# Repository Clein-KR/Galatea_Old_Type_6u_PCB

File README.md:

# Galatea Old Type 6u PCB

<br />

Geonworks에서 판매했던 Studio Kestra의 Galatea 구형 버전과 호환되는 a87 TKL 유니버셜 PCB입니다.

<br />

**Rendering**

<br />

**Prototype**

<br />

**Detail**

<br />

**Compatibility Test**

<br />
<br />

## Supported Layout

<br />

해당 PCB는 ISO 배열을 지원하지 않으며, 6.25u 대신 6u 하단열을 지원합니다.

<br />

<br />

또한 기존의 LED 인디케이터를 모두 버리고 Insert 키 위치에 캡스락 LED 인디케이터를 1개 배치하였습니다. 아래는 Vial의 탭댄스 기능을 활용한 인디케이터 테스트 영상입니다.

<br />

[LED_Indicator_with_Tap_Dance.webm](https://github.com/user-attachments/assets/71b8654c-97a3-42a6-80ce-c4df9c4b528a)

<br />
<br />

## Firmware

<br />

펌웨어는 QMK를 기반으로 Via와 Vial을 지원합니다. 펌웨어 소스코드와 Hex 파일은 [여기](/Firmware)에서 다운로드 받으실 수 있습니다.

<br />

```bash
├── Firmware/
│   ├── clein_galatea_old_type_rev_1_0_via.hex
│   └── clein_galatea_old_type_rev_1_0_vial.hex
└── README.md
```

<br />
<br />

## PCB Guide

<br />

PCB와 호환 보강판 제작에 관련된 가이드 도면은 [여기](/Guide)에서 다운로드 받으실 수 있습니다.

<br />

```bash
├── Guide/
│   ├── PCB_Guideline.dxf
│   ├── PCB_Outline.dxf
│   └── Plate_Guideline.dxf
└── README.md
```

<br />
<br />

## How to Order

<br />

해당 PCB의 프로토타입은 [PCBWay](https://pcbway.com)를 통해 제작되었습니다. 프로토타입 제작에 사용되는 파일들은 [여기](/Production)에서 다운로드 받으실 수 있습니다.

<br />

```bash
├── Production/
│   ├── Galatea_Old_Type_6u_PCB_BOM.csv
│   ├── Galatea_Old_Type_6u_PCB_BOM.xlsx
│   ├── Galatea_Old_Type_6u_PCB_Pos_JLCPCB.csv
│   ├── Galatea_Old_Type_6u_PCB_Pos.csv
│   └── Gerber.zip
└── README.md
```

<br />

아래는 적용된 옵션입니다.

<br />
<br />

## Licence

<br />

해당 프로젝트는 [ai03](https://github.com/ai03-2725) 님의 [KBD8X-MKII-PCB](https://github.com/ai03-2725/KBD8X-MKII-PCB) 프로젝트와 [Joe Scotto](https://github.com/joe-scotto) 님의 [ScottoKeebs](https://github.com/joe-scotto/scottokeebs) 프로젝트를 기반으로 만들어졌습니다. 해당 프로젝트를 활용한 수정, 복제, 배포 등의 활동은 저작자 표시와 함께 비영리적인 목적에 한해서만 가능하며, 라이선스 전문은 [여기](/LICENCE)에서 보실 수 있습니다.

<br />

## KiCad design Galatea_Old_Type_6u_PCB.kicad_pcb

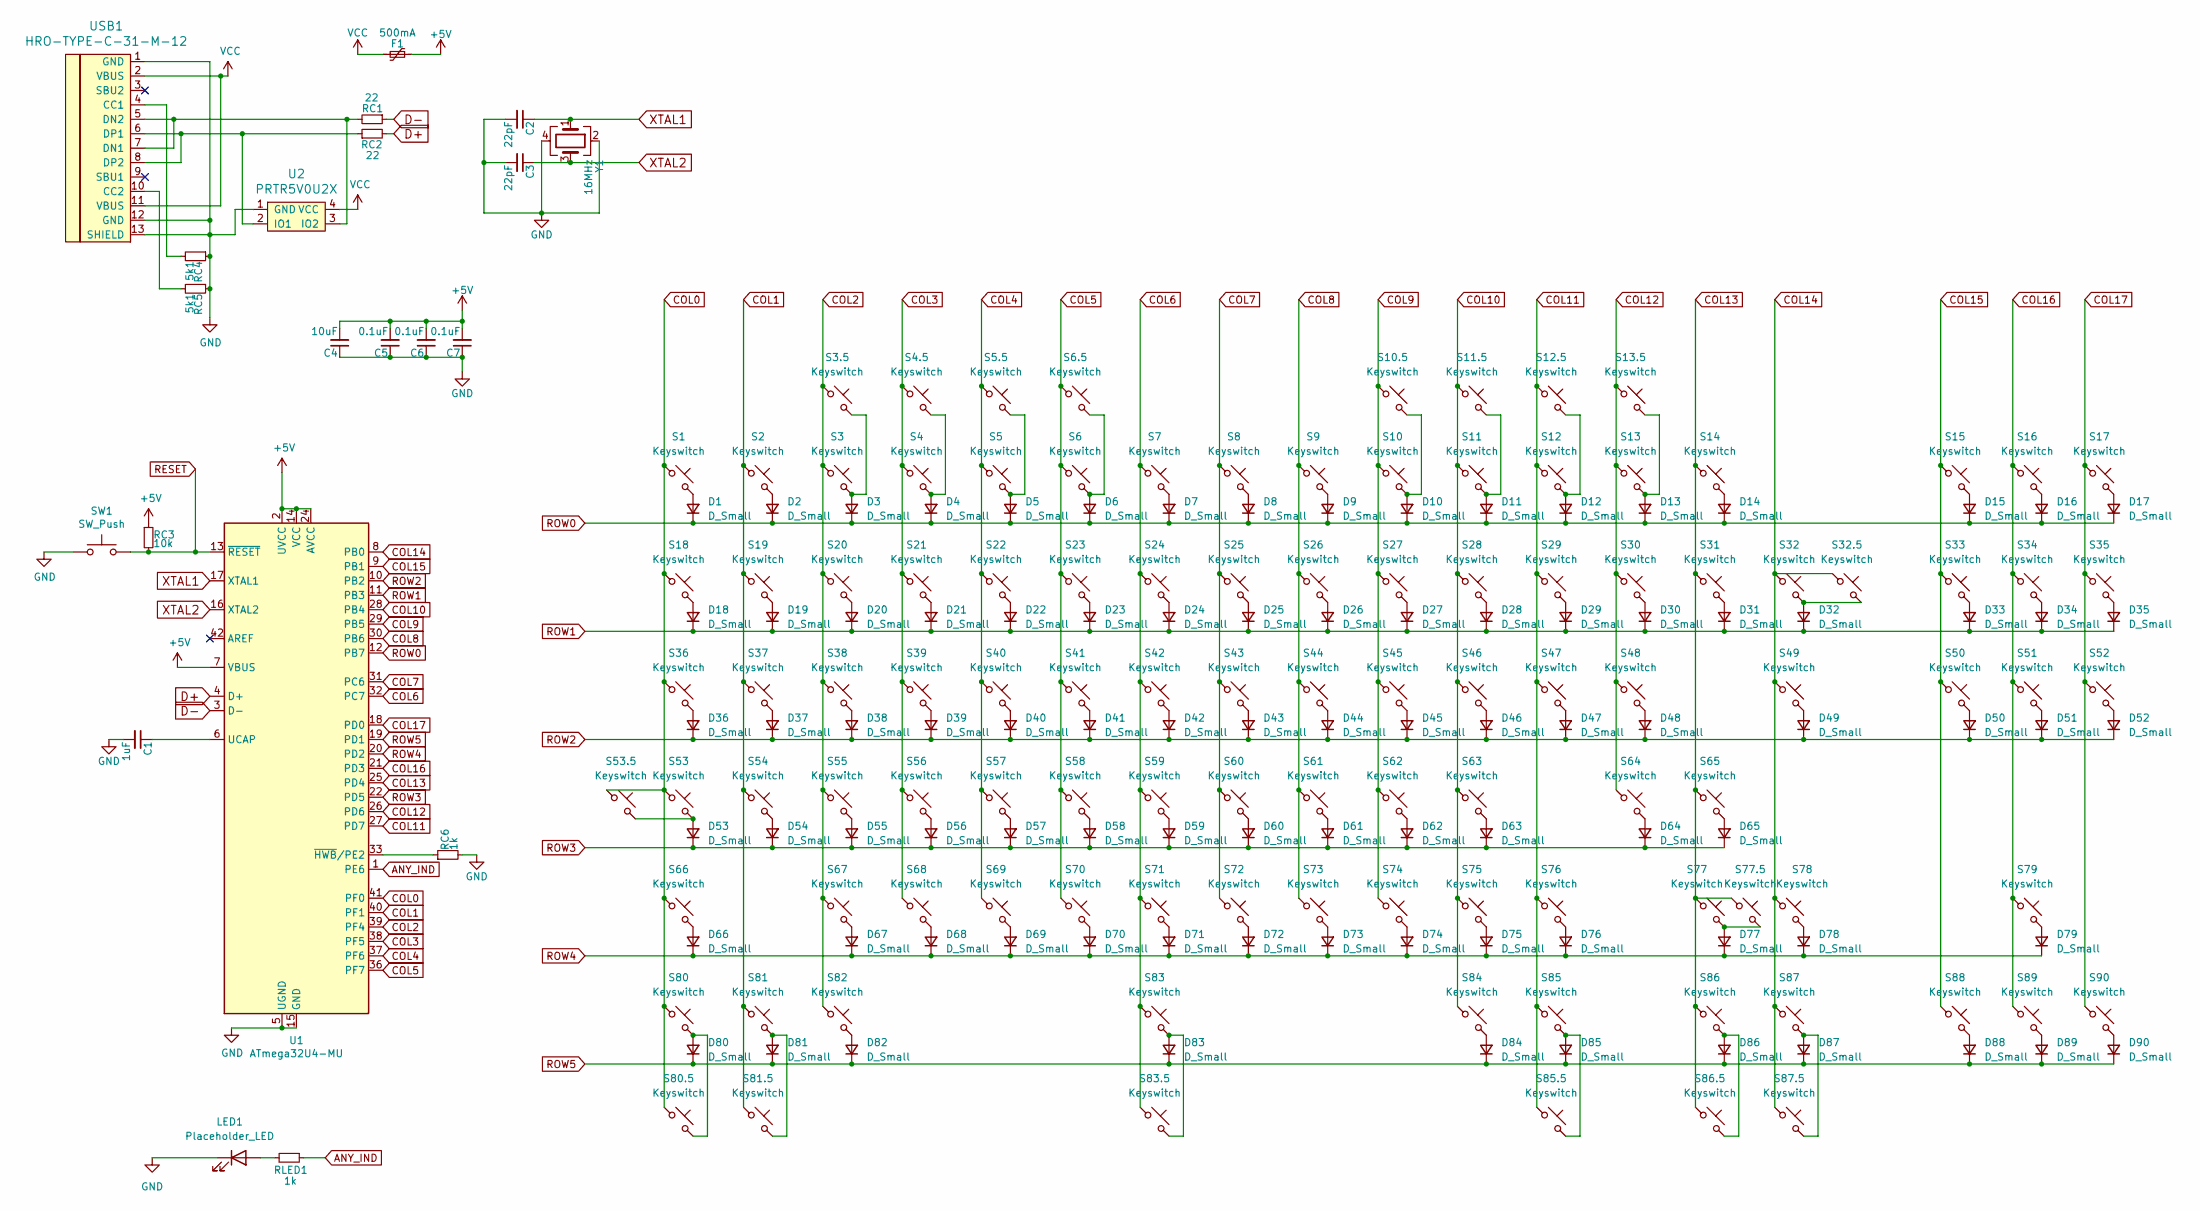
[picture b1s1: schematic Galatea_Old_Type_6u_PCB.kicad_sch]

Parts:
C1: 1uF; C_0603
C2, C3: 22pF; C_0603
C4: 10uF; C_0603
C5, C6, C7: 0.1uF; C_0603
D1, D2, D3, D4, D5, D6, D7, D8, D9, D10, D11, D12, D13, D14, D15, D16, D17, D18, D19, D20, D21, D22, D23, D24, D25, D26, D27, D28, D29, D30, D31, D32, D33, D34, D35, D36, D37, D38, D39, D40, D41, D42, D43, D44, D45, D46, D47, D48, D49, D50, D51, D52, D53, D54, D55, D56, D57, D58, D59, D60, D61, D62, D63, D64, D65, D66, D67, D68, D69, D70, D71, D72, D73, D74, D75, D76, D77, D78, D79, D80, D81, D82, D83, D84, D85, D86, D87, D88, D89, D90: D_Small; D_SOD-123
F1: 500mA; Fuse_1206_3216Metric
LED1: Placeholder_LED; LED_D3.0mm-Pretty
RC1, RC2: 22; R_0603
RC3: 10k; R_0603
RC4, RC5: 5k1; R_0603
RC6: 1k; R_0603
RLED1: 1k; R_0603
S1, S2, S3, S3.5, S4, S4.5, S5, S5.5, S6, S6.5, S7, S8, S9, S10, S10.5, S11, S11.5, S12, S12.5, S13, S13.5, S14, S15, S16, S17, S18, S19, S20, S21, S22, S23, S24, S25, S26, S27, S28, S29, S30, S31, S32, S32.5, S33, S34, S35, S37, S38, S39, S40, S41, S42, S43, S44, S45, S46, S47, S48, S50, S51, S52, S54, S55, S56, S57, S58, S59, S60, S61, S62, S63, S64, S67, S68, S69, S70, S71, S72, S73, S74, S75, S76, S78, S79, S81, S85.5, S86, S88, S89, S90: Keyswitch; MX_PCB_1.00u
S36, S49, S80, S82, S84, S85, S87: Keyswitch; MX_PCB_1.50u
S53, S77: Keyswitch; MX_PCB_1.75u
S53.5, S80.5, S81.5, S86.5, S87.5: Keyswitch; MX_PCB_1.25u
S65, S66: Keyswitch; MX_PCB_2.25u
S77.5: Keyswitch; MX_PCB_2.75u
S83: Keyswitch; MX_PCB_6.00u
S83.5: Keyswitch; MX_PCB_7.00u
SW1: SW_Push; SKQG-1155865
U1: ATmega32U4-MU; QFN-44-1EP_7x7mm_Pitch0.5mm
U2: PRTR5V0U2X; SOT143B
USB1: HRO-TYPE-C-31-M-12; HRO-TYPE-C-31-M-12-Assembly
Y1: 16MHz; Crystal_SMD_3225-4Pin_3.2x2.5mm

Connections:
+5V: C4.2, C5.2, C6.2, C7.2, F1.1, RC3.1, U1.2 (UVCC), U1.7 (VBUS), U1.14 (VCC), U1.24 (AVCC), U1.34 (VCC), U1.44 (AVCC)
ANY_IND: RLED1.1, U1.1 (PE6)
COL0: S1.1, S18.1, S36.1, S53.1, S53.5.1, S66.1, S80.1, S80.5.1, U1.41 (PF0)
COL1: S2.1, S19.1, S37.1, S54.1, S81.1, S81.5.1, U1.40 (PF1)
COL2: S3.1, S3.5.1, S20.1, S38.1, S55.1, S67.1, S82.1, U1.39 (PF4)
COL3: S4.1, S4.5.1, S21.1, S39.1, S56.1, S68.1, U1.38 (PF5)
COL4: S5.1, S5.5.1, S22.1, S40.1, S57.1, S69.1, U1.37 (PF6)
COL5: S6.1, S6.5.1, S23.1, S41.1, S58.1, S70.1, U1.36 (PF7)
COL6: S7.1, S24.1, S42.1, S59.1, S71.1, S83.1, S83.5.1, U1.32 (PC7)
COL7: S8.1, S25.1, S43.1, S60.1, S72.1, U1.31 (PC6)
COL8: S9.1, S26.1, S44.1, S61.1, S73.1, U1.30 (PB6)
COL9: S10.1, S10.5.1, S27.1, S45.1, S62.1, S74.1, U1.29 (PB5)
COL10: S11.1, S11.5.1, S28.1, S46.1, S63.1, S75.1, S84.1, U1.28 (PB4)
COL11: S12.1, S12.5.1, S29.1, S47.1, S76.1, S85.1, S85.5.1, U1.27 (PD7)
COL12: S13.1, S13.5.1, S30.1, S48.1, S64.1, U1.26 (PD6)
COL13: S14.1, S31.1, S65.1, S77.1, S77.5.1, S86.1, S86.5.1, U1.25 (PD4)
COL14: S32.1, S32.5.1, S49.1, S78.1, S87.1, S87.5.1, U1.8 (PB0)
COL15: S15.1, S33.1, S50.1, S88.1, U1.9 (PB1)
COL16: S16.1, S34.1, S51.1, S79.1, S89.1, U1.21 (PD3)
COL17: S17.1, S35.1, S52.1, S90.1, U1.18 (PD0)
D+: RC2.2, U1.4 (D+)
D-: RC1.1, U1.3 (D-)
GND: C1.2, C2.2, C3.2, C4.1, C5.1, C6.1, C7.1, LED1.1 (K), RC4.1, RC5.1, RC6.2, SW1.1, U1.5 (UGND), U1.15 (GND), U1.23 (GND), U1.35 (GND), U1.43 (GND), U1.45 (GND), U2.1 (GND), USB1.1 (GND), USB1.12 (GND), USB1.13 (SHIELD), Y1.2, Y1.4
unnamed: D1.2 (A), S1.2
unnamed: D2.2 (A), S2.2
unnamed: D3.2 (A), S3.2, S3.5.2
unnamed: D4.2 (A), S4.2, S4.5.2
unnamed: D5.2 (A), S5.2, S5.5.2
unnamed: D6.2 (A), S6.2, S6.5.2
unnamed: D7.2 (A), S7.2
unnamed: D8.2 (A), S8.2
unnamed: D9.2 (A), S9.2
unnamed: D10.2 (A), S10.2, S10.5.2
unnamed: D11.2 (A), S11.2, S11.5.2
unnamed: D12.2 (A), S12.2, S12.5.2
unnamed: D13.2 (A), S13.2, S13.5.2
unnamed: D14.2 (A), S14.2
unnamed: D15.2 (A), S15.2
unnamed: D16.2 (A), S16.2
unnamed: D17.2 (A), S17.2
unnamed: D18.2 (A), S18.2
unnamed: D19.2 (A), S19.2
unnamed: D20.2 (A), S20.2
unnamed: D21.2 (A), S21.2
unnamed: D22.2 (A), S22.2
unnamed: D23.2 (A), S23.2
unnamed: D24.2 (A), S24.2
unnamed: D25.2 (A), S25.2
unnamed: D26.2 (A), S26.2
unnamed: D27.2 (A), S27.2
unnamed: D28.2 (A), S28.2
unnamed: D29.2 (A), S29.2
unnamed: D30.2 (A), S30.2
unnamed: D31.2 (A), S31.2
unnamed: D32.2 (A), S32.2, S32.5.2
unnamed: D33.2 (A), S33.2
unnamed: D34.2 (A), S34.2
unnamed: D35.2 (A), S35.2
unnamed: D36.2 (A), S36.2
unnamed: D37.2 (A), S37.2
unnamed: D38.2 (A), S38.2
unnamed: D39.2 (A), S39.2
unnamed: D40.2 (A), S40.2
unnamed: D41.2 (A), S41.2
unnamed: D42.2 (A), S42.2
unnamed: D43.2 (A), S43.2
unnamed: D44.2 (A), S44.2
unnamed: D45.2 (A), S45.2
unnamed: D46.2 (A), S46.2
unnamed: D47.2 (A), S47.2
unnamed: D48.2 (A), S48.2
unnamed: D49.2 (A), S49.2
unnamed: D50.2 (A), S50.2
unnamed: D51.2 (A), S51.2
unnamed: D52.2 (A), S52.2
unnamed: D53.2 (A), S53.2, S53.5.2
unnamed: D54.2 (A), S54.2
unnamed: D55.2 (A), S55.2
unnamed: D56.2 (A), S56.2
unnamed: D57.2 (A), S57.2
unnamed: D58.2 (A), S58.2
unnamed: D59.2 (A), S59.2
unnamed: D60.2 (A), S60.2
unnamed: D61.2 (A), S61.2
unnamed: D62.2 (A), S62.2
unnamed: D63.2 (A), S63.2
unnamed: D64.2 (A), S64.2
unnamed: D65.2 (A), S65.2
unnamed: D66.2 (A), S66.2
unnamed: D67.2 (A), S67.2
unnamed: D68.2 (A), S68.2
unnamed: D69.2 (A), S69.2
unnamed: D70.2 (A), S70.2
unnamed: D71.2 (A), S71.2
unnamed: D72.2 (A), S72.2
unnamed: D73.2 (A), S73.2
unnamed: D74.2 (A), S74.2
unnamed: D75.2 (A), S75.2
unnamed: D76.2 (A), S76.2
unnamed: D77.2 (A), S77.2, S77.5.2
unnamed: D78.2 (A), S78.2
unnamed: D79.2 (A), S79.2
unnamed: D80.2 (A), S80.2, S80.5.2
unnamed: D81.2 (A), S81.2, S81.5.2
unnamed: D82.2 (A), S82.2
unnamed: D83.2 (A), S83.2, S83.5.2
unnamed: D84.2 (A), S84.2
unnamed: D85.2 (A), S85.2, S85.5.2
unnamed: D86.2 (A), S86.2, S86.5.2
unnamed: D87.2 (A), S87.2, S87.5.2
unnamed: D88.2 (A), S88.2
unnamed: D89.2 (A), S89.2
unnamed: D90.2 (A), S90.2
unnamed: LED1.2 (A), RLED1.2
unnamed: C1.1, U1.6 (UCAP)
unnamed: RC6.1, U1.33 (~HWB/PE2)
unnamed: RC2.1, U2.2 (IO1), USB1.6 (DP1), USB1.8 (DP2)
unnamed: RC1.2, U2.3 (IO2), USB1.5 (DN2), USB1.7 (DN1)
unnamed: RC4.2, USB1.4 (CC1)
unnamed: RC5.2, USB1.10 (CC2)
RESET: RC3.2, SW1.2, U1.13 (~RESET)
ROW0: D1.1 (K), D2.1 (K), D3.1 (K), D4.1 (K), D5.1 (K), D6.1 (K), D7.1 (K), D8.1 (K), D9.1 (K), D10.1 (K), D11.1 (K), D12.1 (K), D13.1 (K), D14.1 (K), D15.1 (K), D16.1 (K), D17.1 (K), U1.12 (PB7)
ROW1: D18.1 (K), D19.1 (K), D20.1 (K), D21.1 (K), D22.1 (K), D23.1 (K), D24.1 (K), D25.1 (K), D26.1 (K), D27.1 (K), D28.1 (K), D29.1 (K), D30.1 (K), D31.1 (K), D32.1 (K), D33.1 (K), D34.1 (K), D35.1 (K), U1.11 (PB3)
ROW2: D36.1 (K), D37.1 (K), D38.1 (K), D39.1 (K), D40.1 (K), D41.1 (K), D42.1 (K), D43.1 (K), D44.1 (K), D45.1 (K), D46.1 (K), D47.1 (K), D48.1 (K), D49.1 (K), D50.1 (K), D51.1 (K), D52.1 (K), U1.10 (PB2)
ROW3: D53.1 (K), D54.1 (K), D55.1 (K), D56.1 (K), D57.1 (K), D58.1 (K), D59.1 (K), D60.1 (K), D61.1 (K), D62.1 (K), D63.1 (K), D64.1 (K), D65.1 (K), U1.22 (PD5)
ROW4: D66.1 (K), D67.1 (K), D68.1 (K), D69.1 (K), D70.1 (K), D71.1 (K), D72.1 (K), D73.1 (K), D74.1 (K), D75.1 (K), D76.1 (K), D77.1 (K), D78.1 (K), D79.1 (K), U1.20 (PD2)
ROW5: D80.1 (K), D81.1 (K), D82.1 (K), D83.1 (K), D84.1 (K), D85.1 (K), D86.1 (K), D87.1 (K), D88.1 (K), D89.1 (K), D90.1 (K), U1.19 (PD1)
VCC: F1.2, U2.4 (VCC), USB1.2 (VBUS), USB1.11 (VBUS)
XTAL1: C2.1, U1.17 (XTAL1), Y1.1
XTAL2: C3.1, U1.16 (XTAL2), Y1.3

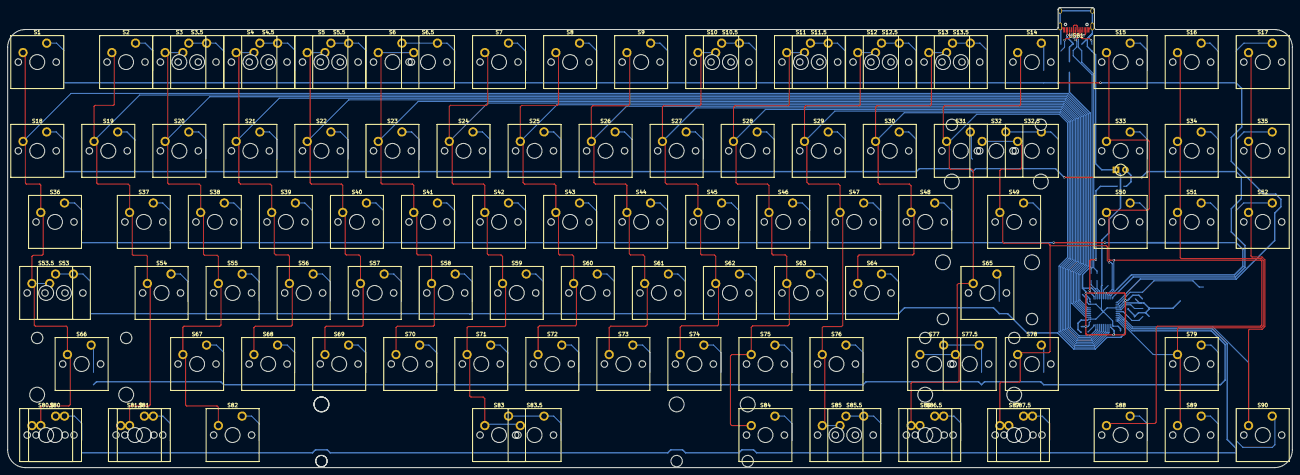
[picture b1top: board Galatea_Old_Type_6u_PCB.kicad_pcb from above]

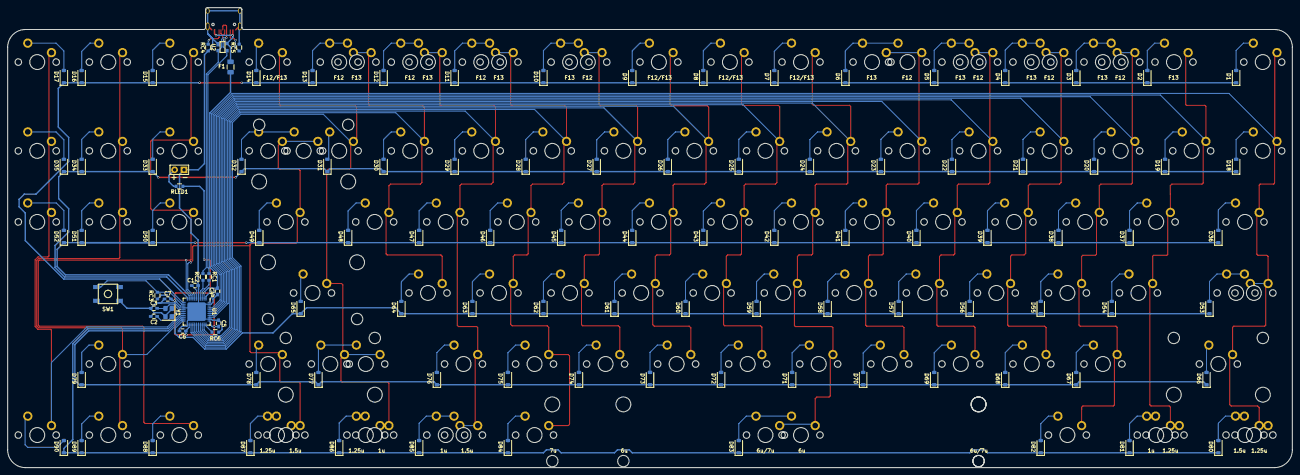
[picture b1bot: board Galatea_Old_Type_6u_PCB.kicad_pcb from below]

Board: 2 copper layers, 344.5 x 123.3 mm, 218 parts (109 on the bottom side), 130 nets.

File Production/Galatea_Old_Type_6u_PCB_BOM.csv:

Component,Comment,Description,Part,Designator,Footprint,Pins,Quantity Per PCB,Manufacturer,Mfg Part #,LCSC Part #
1,1uF 20% ≥15V X5R/X7R,"Capacitor, Ceramic, 0603",C_Small,C1,C_0603,2,1,HRE,CGA0603X5R105K160JT,C6119849
2,22pF 5% ≥15V C0G,"Capacitor, Ceramic, 0603",C_Small,"C2, C3",C_0603,2,2,KEMET,C0603C220J4GAC7867,C561800
3,10uF 20% ≥15V X5R/X7R,"Capacitor, Ceramic, 0603",C_Small,C4,C_0603,2,1,HRE,CGA0603X5R106M160JT,C6119814
4,0.1uF 20% ≥15V X5R/X7R,"Capacitor, Ceramic, 0603",C_Small,"C5, C6, C7",C_0603,2,3,YAGEO,CC0603KRX7R7BB104,C108079
5,Generic,"Diode, SOD-123",D_Small,"D1, D2, D3, D4, D5, D6, D7, D8, D9, D10, D11, D12, D13, D14, D15, D16, D17, D18, D19, D20, D21, D22, D23, D24, D25, D26, D27, D28, D29, D30, D31, D32, D33, D34, D35, D36, D37, D38, D39, D40, D41, D42, D43, D44, D45, D46, D47, D48, D49, D50, D51, D52, D53, D54, D55, D56, D57, D58, D59, D60, D61, D62, D63, D64, D65, D66, D67, D68, D69, D70, D71, D72, D73, D74, D75, D76, D77, D78, D79, D80, D81, D82, D83, D84, D85, D86, D87, D88, D89, D90",D_SOD-123,2,90,Slkor(SLKORMICRO Elec.),1N4148W,C444720
6,500mA ≥15V 500mA_Hold 1A_Trip,"Polyfuse, 1206",Polyfuse_Small,F1,Fuse_SMD1206_Wave,2,1,BHFUSE,BSMD1206-050-16V,C883124
7,22 1%,"Resistor, Generic, 0603",R_Small,"RC1, RC2",R_0603,2,2,YAGEO,RC0603FR-0722RL,C107701
8,10k 1%,"Resistor, Generic, 0603",R_Small,RC3,R_0603,2,1,YAGEO,RC0603FR-0710KL,C98220
9,5.1k 1%,"Resistor, Generic, 0603",R_Small,"RC4, RC5",R_0603,2,2,YAGEO,RC0603FR-075K1L,C105580
10,1k 1%,"Resistor, Generic, 0603",R_Small,"RC6, RLED1",R_0603,2,2,YAGEO,RC0603FR-071KL,C22548
11,SMT 5.2 x 5.2 x 1.5mm,Push button,SW_Push,SW1,SKQG-1155865,4,1,ALPSALPINE,SKQGABE010,C115351
12,ATmega32U4-MU,MCU,ATmega32U4-MU,U1,QFN-44-1EP_7x7mm_Pitch0.5mm,45,1,MICROCHIP,ATMEGA32U4-MU,C112161
13,PRTR5V0U2X,ESD Protection IC,PRTR5V0U2X,U2,SOT143B,4,1,Nexperia,PRTR5V0U2X,C12333
14,HRO-TYPE-C-31-M-12,USB Type-C Connector,HRO-TYPE-C-31-M-12,USB1,HRO-TYPE-C-31-M-12-Assembly,16,1,Korean Hroparts Elec,TYPE-C-31-M-12,C165948
15,16MHz,"Crystal, 3.2 x 2.5mm (3225-4)",Crystal_GND24,Y1,Crystal_SMD_3225-4pin_3.2x2.5mm,4,1,Huiyuan crystal,HY16MSMD3225OB1R30,C7275098

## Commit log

2025-11-09 Add PCB files
2025-11-28 Add firmware files
2025-11-29 Add README & Licence

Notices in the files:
README.md:
https://mirrors.creativecommons.org/presskit/icons/cc.svg?ref=chooser-v1
https://mirrors.creativecommons.org/presskit/icons/by.svg?ref=chooser-v1
https://mirrors.creativecommons.org/presskit/icons/nc.svg?ref=chooser-v1
https://mirrors.creativecommons.org/presskit/icons/sa.svg?ref=chooser-v1
